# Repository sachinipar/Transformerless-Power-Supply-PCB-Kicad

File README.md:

# 220V AC to 5V DC Transformerless Power Supply

* **Input:** 220V AC, 50/60Hz
* **Output:** 5V DC
* **Output Current:** ~100–150mA
* **Type:** Capacitive Dropper, Non-Isolated
* **Regulator:** LM7805

## Components

* **C4 – 2.2µF:** Capacitive voltage/current dropper
* **R3 – 1MΩ:** Bleeder resistor
* **D1–D4 – 1N4007:** Bridge rectifier
* **C1 – 0.1µF:** Noise filtering
* **C2 – 1000µF:** DC smoothing
* **U1 – LM7805:** 5V voltage regulator
* **C3 – 470µF:** Output filtering
* **D7:** Power indicator LED

## Features

* Compact transformerless design
* Low-cost components
* Suitable for low-power loads
* Regulated 5V DC output

## ⚠️ Safety

* **Non-isolated circuit — dangerous mains voltage is present.**
* Do not touch the circuit while connected to 220V AC.
* Use an **X2-rated capacitor** for C4.
* Do not connect the output to USB, computers or other user-accessible equipment.
* Use a proper isolated AC-DC supply when electrical isolation is required.

> **Warning:** Working with mains voltage can cause serious injury or death. Build and test only with proper knowledge and safety precautions.

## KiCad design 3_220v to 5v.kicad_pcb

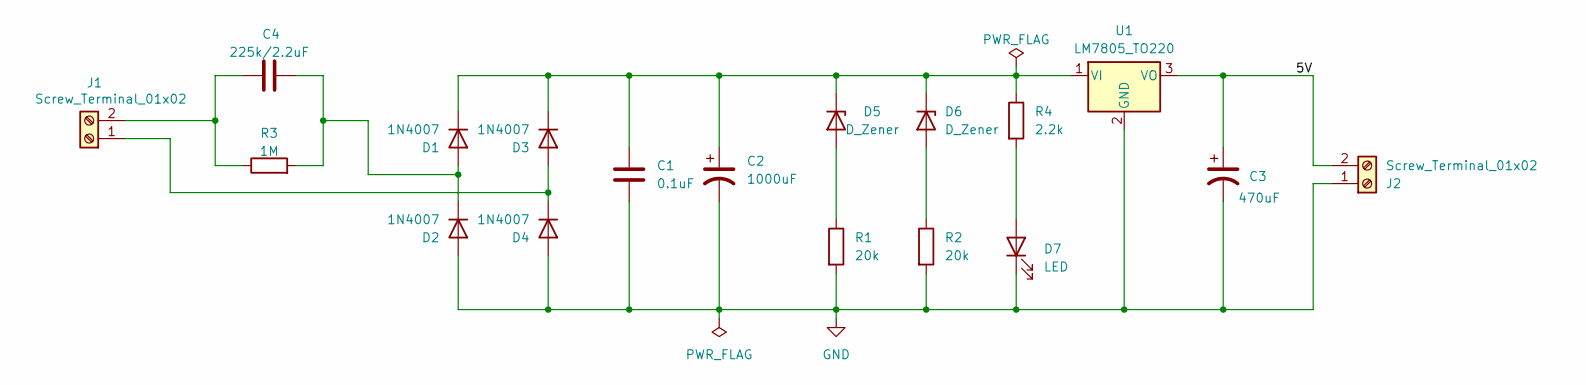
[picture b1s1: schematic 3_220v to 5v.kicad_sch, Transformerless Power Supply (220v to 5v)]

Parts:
C1: 0.1uF; C_Disc_D4.7mm_W2.5mm_P5.00mm
C2: 1000uF; CP_Radial_D10.0mm_P5.00mm
C3: 470uF; CP_Radial_D10.0mm_P3.80mm
C4: 225k/2.2uF; C_Rect_L18.0mm_W6.0mm_P15.00mm_FKS3_FKP3
D1, D2, D3, D4: 1N4007; D_DO-41_SOD81_P10.16mm_Horizontal
D5, D6: D_Zener; D_A-405_P7.62mm_Horizontal
D7: LED; LED_D5.0mm
J1, J2: Screw_Terminal_01x02; TerminalBlock_MaiXu_MX126-5.0-02P_1x02_P5.00mm
R1, R2: 20k; R_Axial_DIN0207_L6.3mm_D2.5mm_P7.62mm_Horizontal
R3: 1M; R_Axial_DIN0207_L6.3mm_D2.5mm_P7.62mm_Horizontal
R4: 2.2k; R_Axial_DIN0207_L6.3mm_D2.5mm_P7.62mm_Horizontal
U1: LM7805_TO220; TO-220-3_Vertical

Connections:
/5V: C3.1, J2.2, U1.3 (VO)
GND: C1.1, C2.2, C3.2, D2.2 (A), D4.2 (A), D7.1 (K), J2.1, R1.2, R2.2, U1.2 (GND)
unnamed: C4.2, D1.2 (A), D2.1 (K), R3.2
unnamed: C1.2, C2.1, D1.1 (K), D3.1 (K), D5.1 (K), D6.1 (K), R4.1, U1.1 (VI)
unnamed: D3.2 (A), D4.1 (K), J1.1
unnamed: D5.2 (A), R1.1
unnamed: D6.2 (A), R2.1
unnamed: D7.2 (A), R4.2
unnamed: C4.1, J1.2, R3.1

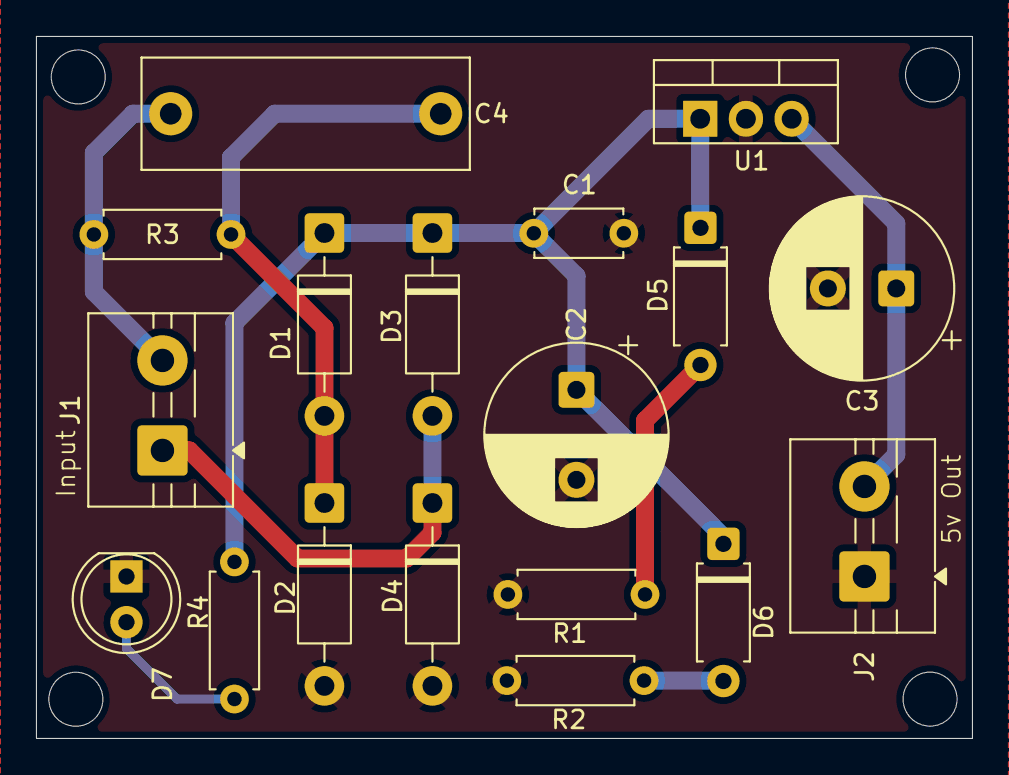
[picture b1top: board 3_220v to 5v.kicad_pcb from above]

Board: 2 copper layers, 52.0 x 39.0 mm, 18 parts (0 on the bottom side), 9 nets.
